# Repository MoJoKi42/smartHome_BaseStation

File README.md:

# smartHome_BaseStation

This Smart Home base station is built around an **ESP32** as the controller and uses an **RFM69HW** 433 MHz radio module for the wireless communication with sensors and actuators. For network communication with an MQTT server, a W5500 Ethernet PHY is used. Status information is displayed via status LEDs and an **I2C OLED display**. To improve the range of the radio system, I used an external dipol antenna. The PCB antenna works okay, but the range is not sufficient for the sensors outside my flat.

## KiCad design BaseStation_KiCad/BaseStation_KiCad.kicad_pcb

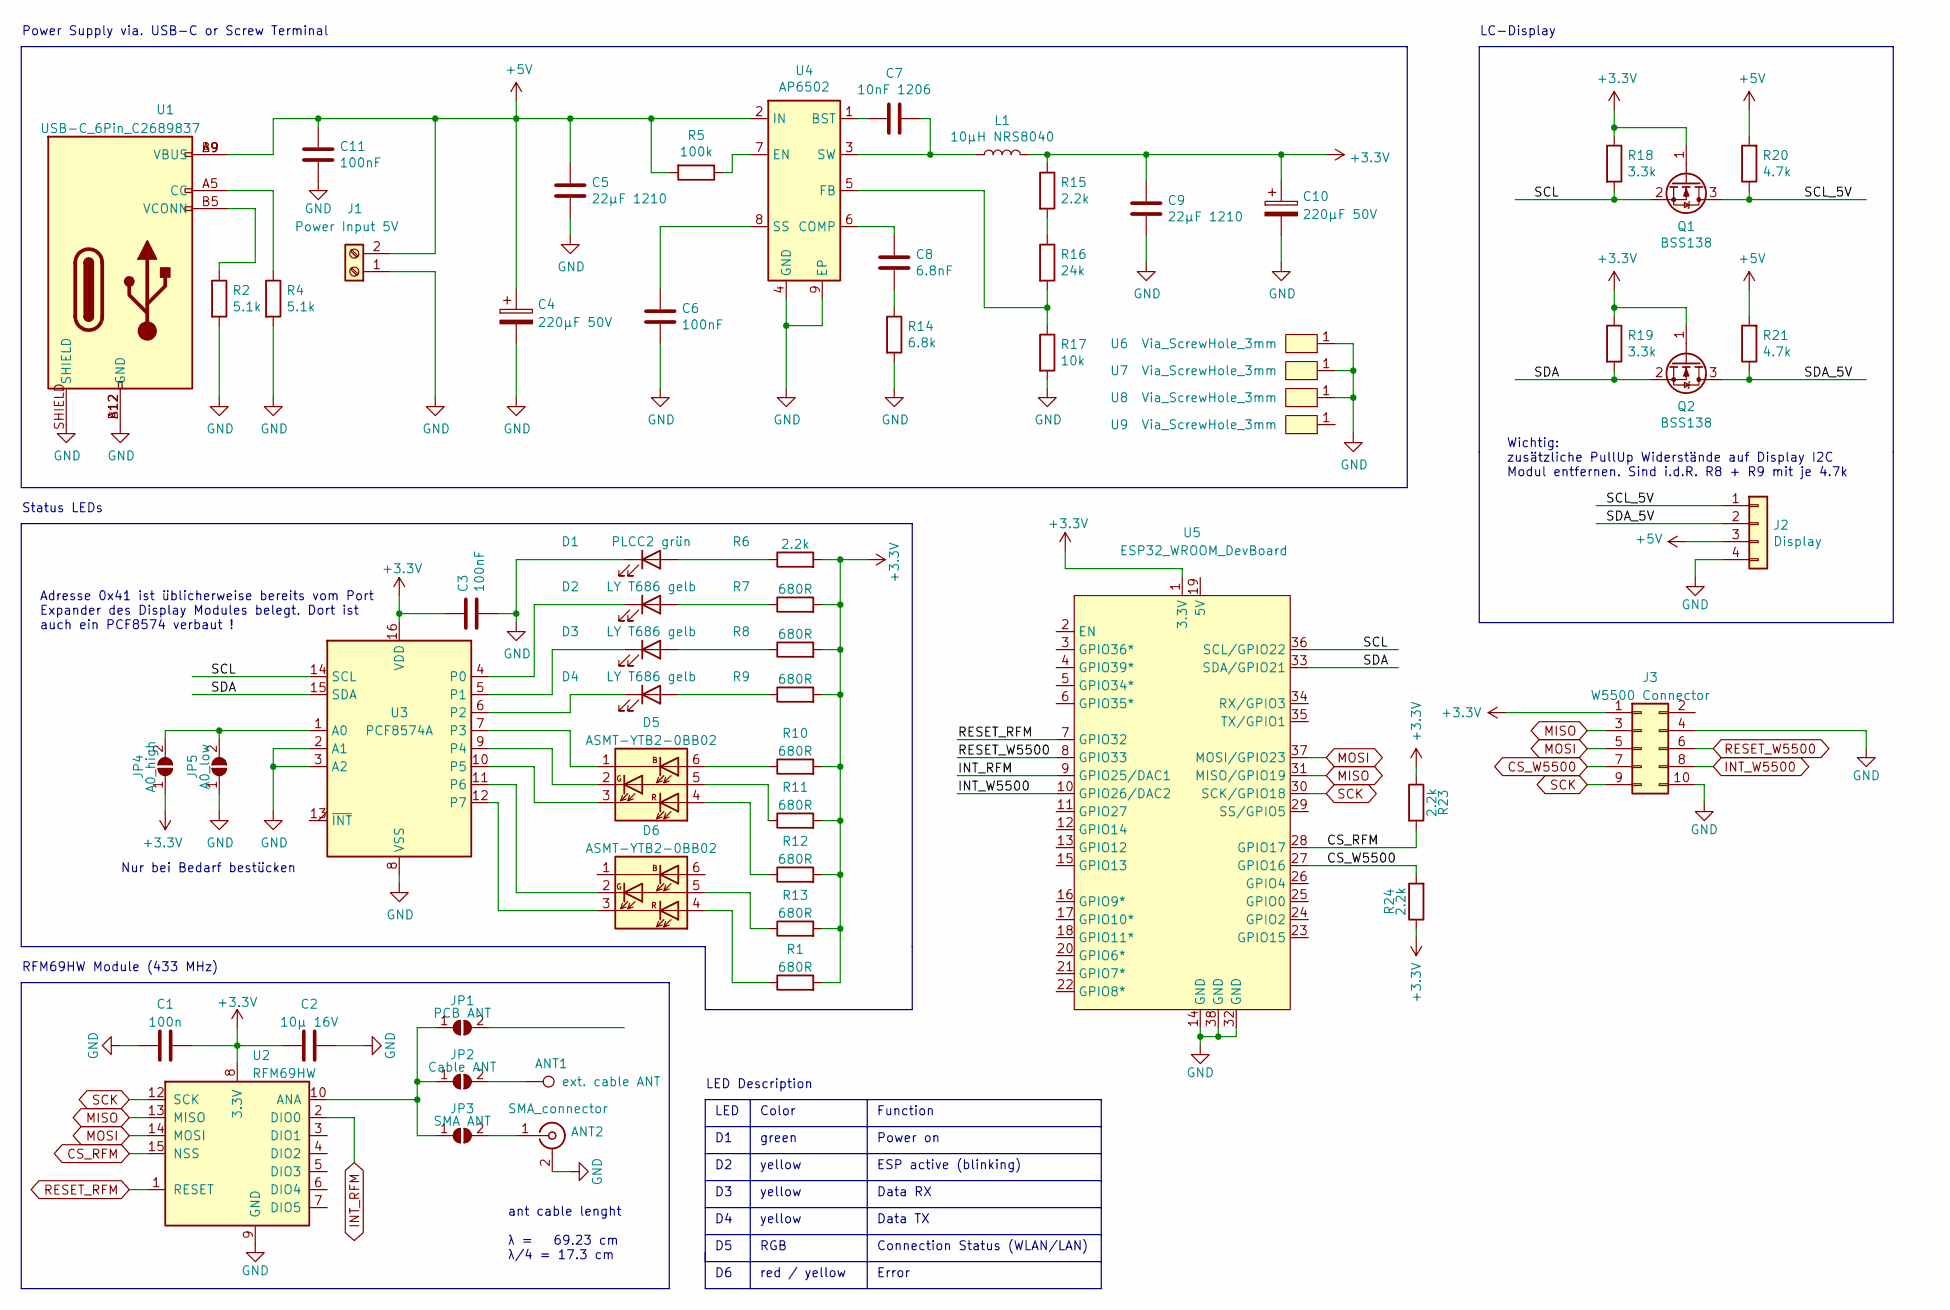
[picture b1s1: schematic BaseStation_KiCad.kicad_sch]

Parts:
ANT1: ext. cable ANT; TestPoint_Pad_3.0x3.0mm
ANT2: SMA_connector; SMA_Wurth_60312002114503_Vertical
C1: 100n; C_0805_2012Metric_Pad1.18x1.45mm_HandSolder
C2: 10µ 16V; C_1210_3225Metric_Pad1.33x2.70mm_HandSolder
C3, C6, C11: 100nF; C_0805_2012Metric_Pad1.18x1.45mm_HandSolder
C4, C10: 220µF 50V; C_Elec_10x10.2
C5, C9: 22µF 1210; C_1210_3225Metric_Pad1.33x2.70mm_HandSolder
C7: 10nF 1206; C_1206_3216Metric_Pad1.33x1.80mm_HandSolder
C8: 6.8nF; C_0805_2012Metric_Pad1.18x1.45mm_HandSolder
D1: PLCC2 grün; LED_PLCC-2_3.4x3.0mm_AK
D2, D3, D4: LY T686 gelb; LED_PLCC-2_3.4x3.0mm_AK
D5, D6: ASMT-YTB2-0BB02; LED_Avago_PLCC6_3x2.8mm
J1: Power Input 5V; TerminalBlock_RND_205-00001_1x02_P5.00mm_Horizontal
J2: Display; JST_XH_B4B-XH-A_1x04_P2.50mm_Vertical
J3: W5500 Connector; IDC-Header_2x05_P2.54mm_Vertical
JP1: PCB ANT; SolderJumper-2_P1.3mm_Open_RoundedPad1.0x1.5mm
JP2: Cable ANT; SolderJumper-2_P1.3mm_Open_RoundedPad1.0x1.5mm
JP3: SMA ANT; SolderJumper-2_P1.3mm_Open_RoundedPad1.0x1.5mm
JP4: A0_high; SolderJumper-2_P1.3mm_Open_RoundedPad1.0x1.5mm
JP5: A0_low; SolderJumper-2_P1.3mm_Open_RoundedPad1.0x1.5mm
L1: 10µH NRS8040; L_Taiyo-Yuden_NR-80xx_HandSoldering
Q1, Q2: BSS138; SOT-23
R1, R7, R8, R9, R10, R11, R12, R13: 680R; R_0805_2012Metric_Pad1.20x1.40mm_HandSolder
R2, R4: 5.1k; R_0805_2012Metric_Pad1.20x1.40mm_HandSolder
R5: 100k; R_0805_2012Metric_Pad1.20x1.40mm_HandSolder
R6, R15, R23, R24: 2.2k; R_0805_2012Metric_Pad1.20x1.40mm_HandSolder
R14: 6.8k; R_0805_2012Metric_Pad1.20x1.40mm_HandSolder
R16: 24k; R_0805_2012Metric_Pad1.20x1.40mm_HandSolder
R17: 10k; R_0805_2012Metric_Pad1.20x1.40mm_HandSolder
R18, R19: 3.3k; R_0805_2012Metric_Pad1.20x1.40mm_HandSolder
R20, R21: 4.7k; R_0805_2012Metric_Pad1.20x1.40mm_HandSolder
U1: USB-C_6Pin_C2689837
U2: RFM69HW; HOPERF_RFM69HW
U3: PCF8574A; SOIC-16W_7.5x10.3mm_P1.27mm
U4: AP6502; SOIC-8-1EP_3.9x4.9mm_P1.27mm_EP2.29x3mm
U5: ESP32_WROOM_DevBoard
U6, U7, U8, U9: Via_ScrewHole_3mm

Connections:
+3.3V: C1.2, C2.1, C3.1, C9.1, C10.1, J3.1, JP4.1 (A), L1.2, Q1.1 (G), Q2.1 (G), R1.2, R6.2, R7.2, R8.2, R9.2, R10.2, R11.2, R12.2, R13.2, R15.1, R18.1, R19.1, R23.1, R24.1, U2.8 (3.3V), U3.16 (VDD), U5.1 (3.3V)
+5V: C4.1, C5.1, C11.1, J1.2, J2.3, R5.2, R20.2, R21.2, U1.A9 (VBUS), U1.B9 (VBUS), U4.2 (IN)
/SCL: Q1.2 (S), R18.2, U3.14 (SCL), U5.36 (SCL/GPIO22)
/SCL_5V: J2.1, Q1.3 (D), R20.1
/SDA: Q2.2 (S), R19.2, U3.15 (SDA), U5.33 (SDA/GPIO21)
/SDA_5V: J2.2, Q2.3 (D), R21.1
CS_RFM: R23.2, U2.15 (NSS), U5.28 (GPIO17)
CS_W5500: J3.7, R24.2, U5.27 (GPIO16)
GND: ANT2.2 (Ext), C1.1, C2.2, C3.2, C4.2, C5.2, C6.2, C9.2, C10.2, C11.2, D1.1 (K), J1.1, J2.4, J3.4, J3.10, JP5.1 (A), R2.2, R4.2, R14.2, R17.2, U1.A12 (GND), U1.B12 (GND), U1.SHIELD, U2.9 (GND), U2.11 (GND), U3.2 (A1), U3.3 (A2), U3.8 (VSS), U4.4 (GND), U4.9 (EP), U5.14 (GND), U5.32 (GND), U5.38 (GND), U6.1, U7.1, U8.1
INT_RFM: U2.2 (DIO0), U5.9 (GPIO25/DAC1)
INT_W5500: J3.8, U5.10 (GPIO26/DAC2)
MISO: J3.3, U2.13 (MISO), U5.31 (MISO/GPIO19)
MOSI: J3.5, U2.14 (MOSI), U5.37 (MOSI/GPIO23)
unnamed: ANT1.1, JP2.2 (B)
unnamed: ANT2.1 (In), JP3.2 (B)
unnamed: C6.1, U4.8 (SS)
unnamed: C7.1, L1.1, U4.3 (SW)
unnamed: C7.2, U4.1 (BST)
unnamed: C8.1, U4.6 (COMP)
unnamed: C8.2, R14.1
unnamed: D1.2 (A), R6.1
unnamed: D2.1 (K), U3.4 (P0)
unnamed: D2.2 (A), R7.1
unnamed: D3.1 (K), U3.5 (P1)
unnamed: D3.2 (A), R8.1
unnamed: D4.1 (K), U3.6 (P2)
unnamed: D4.2 (A), R9.1
unnamed: D5.1 (KB), U3.7 (P3)
unnamed: D5.2 (KG), U3.9 (P4)
unnamed: D5.3 (KR), U3.10 (P5)
unnamed: D5.4 (AR), R12.1
unnamed: D5.5 (AG), R11.1
unnamed: D5.6 (AB), R10.1
unnamed: D6.2 (KG), U3.11 (P6)
unnamed: D6.3 (KR), U3.12 (P7)
unnamed: D6.4 (AR), R1.1
unnamed: D6.5 (AG), R13.1
unnamed: JP1.1 (A), JP2.1 (A), JP3.1 (A), U2.10 (ANA)
unnamed: R2.1, U1.B5 (VCONN)
unnamed: R4.1, U1.A5 (CC)
unnamed: R5.1, U4.7 (EN)
unnamed: R15.2, R16.1
unnamed: R16.2, R17.1, U4.5 (FB)
unnamed: JP4.2 (B), JP5.2 (B), U3.1 (A0)
RESET_RFM: U2.1 (RESET), U5.7 (GPIO32)
RESET_W5500: J3.6, U5.8 (GPIO33)
SCK: J3.9, U2.12 (SCK), U5.30 (SCK/GPIO18)

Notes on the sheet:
RFM69HW Module (433 MHz)
Connection Status (WLAN/LAN)
Wichtig: zusätzliche PullUp Widerstände auf Display I2C Modul entfernen. Sind i.d.R. R8 + R9 mit je 4.7k
Function
LED
ESP active (blinking)
RGB
LC-Display
green
ant cable lenght λ = 69.23 cm λ/4 = 17.3 cm
Power Supply via. USB-C or Screw Terminal
yellow
LED Description
Data RX
red / yellow
Error
Adresse 0x41 ist üblicherweise bereits vom Port Expander des Display Modules belegt. Dort ist auch ein PCF8574 verbaut !
Status LEDs
Color
Nur bei Bedarf bestücken
Data TX
Power on

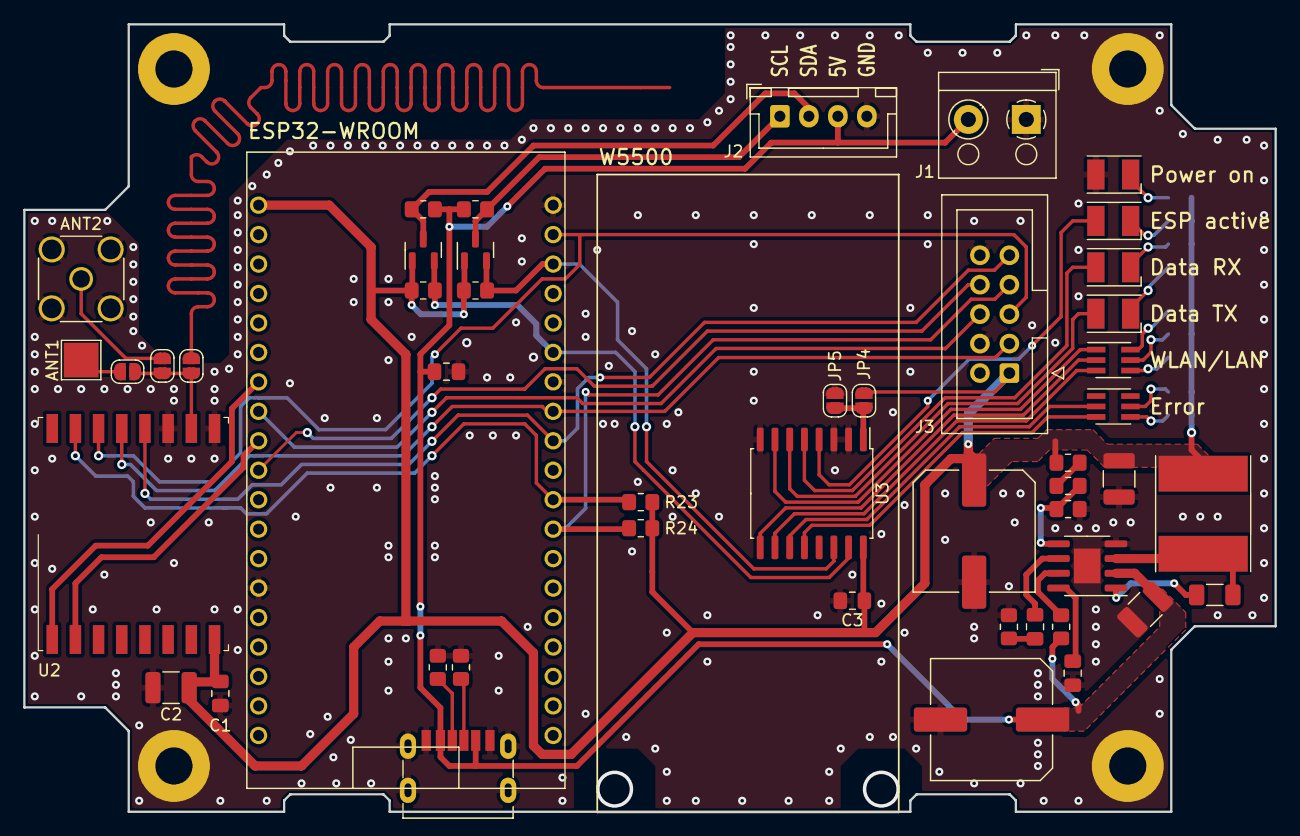
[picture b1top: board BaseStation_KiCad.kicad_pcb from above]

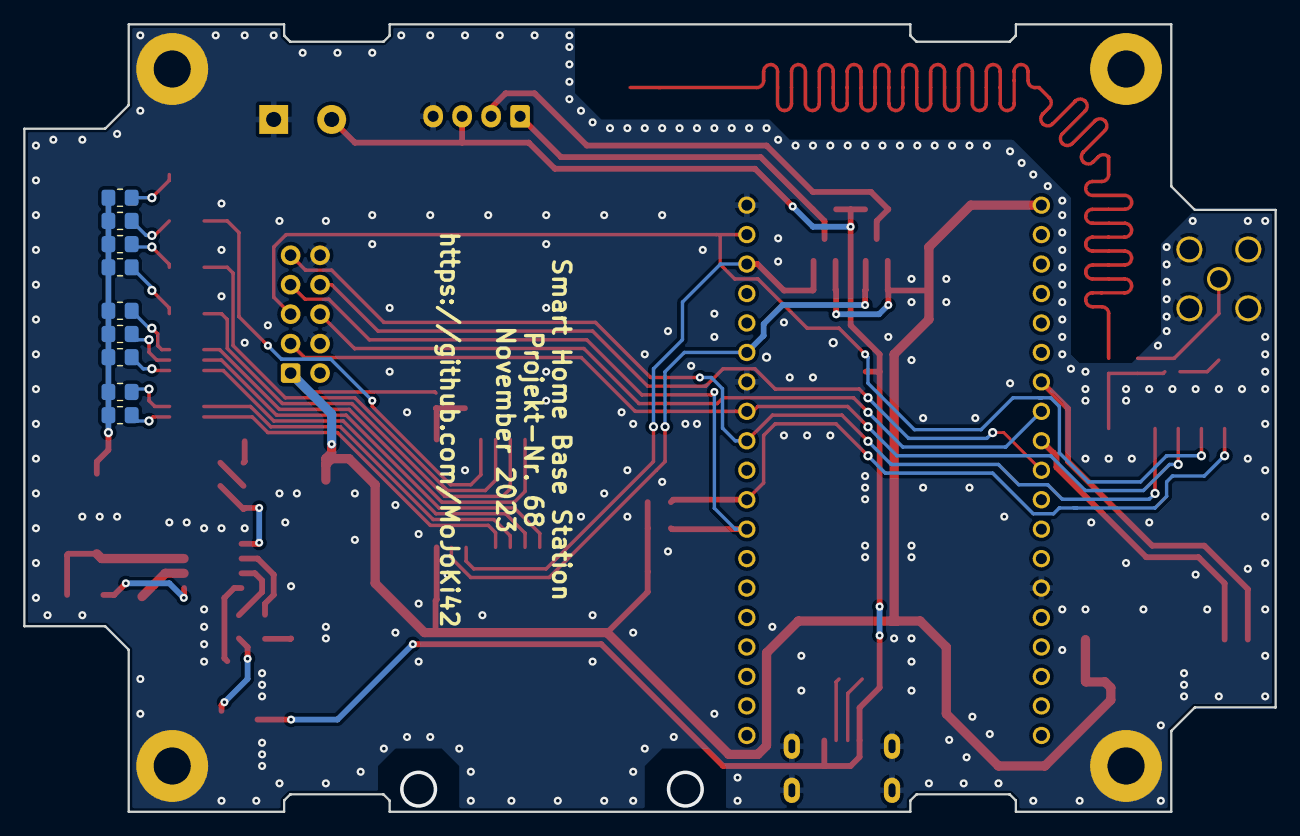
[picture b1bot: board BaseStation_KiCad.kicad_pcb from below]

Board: 2 copper layers, 107.9 x 67.9 mm, 61 parts (9 on the bottom side), 47 nets.

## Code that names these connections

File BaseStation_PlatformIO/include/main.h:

#define LED_status_ESP_active   0
#define LED_status_data_RX      1
#define LED_status_data_TX      2
#define LED_status_LAN_blue     3
#define LED_status_LAN_green    4
#define LED_status_LAN_red      5
#define LED_status_error_green  6
#define LED_status_error_red    7

#define PIN_CS_RFM      17
#define PIN_INT_RFM     25
#define PIN_CS_W5500    16
#define PIN_BUTTON      4


#define NODEID          0x01    // keep UNIQUE for each node on same network
#define NETWORKID       33      // keep IDENTICAL on all nodes that talk to each other
#define FREQUENCY       RF69_433MHZ
#define ENCRYPTKEY      "1234567812345678"


// MQTT / Ethernet
// Source: https://github.com/jozala/ESP32_W5500_MQTT
#define ETHERNET_MAC            "FF:FF:FF:FF:FF:FF" // Ethernet MAC address
#define ETHERNET_IP             "192.168.150.100"   // IP address of Ethernet connection
#define ETHERNET_RESET_PIN      33                  // ESP32 pin where reset pin from W5500 is connected
#define ETHERNET_CS_PIN         16                  // ESP32 pin where CS pin from W5500 is connected
#define MQTT_HOSTNAME           "192.168.150.101"
#define MQTT_PORT                   1883
#define MQTT_PUBLISH_INTERVAL_MS    250


// MQTT tree example
/*
base_0x01_rx
           ├── nodes_0x10
           │            ├── node_0x11 = {...}
           │            └── node_0x12 = {...}
           └── nodes_0x20
                        ├── node_0x21 = {...}
                        └── node_0x22 = {...}
base_0x01_tx
           ├── node_0x11 = {...}
           └── node_0x32 = {...}

base_0x01_stats
              ├── uptime = 
              ├── packets_rx = 
              └── packets_tx =
*/

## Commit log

2025-03-18 initial
